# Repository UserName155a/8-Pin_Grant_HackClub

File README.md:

BOM found in .csv file

Log excluding most of the part hunting time:

11/10 ~23:00 - 11/11 ~00:40 : Working on Joystick project to use as a mouse cursor controller 

11/11 ~9:XX - 12:20? : Figuring out what parts to use and some wiring on schematics (50/50 each I think)

11/11 2:04 - 2:36 : Mapped out schematics and finalized

11/12 20:22 - 23:45 : Trying to figure out how PCB editor works and trying to connect traces (countless redos)

11/13 12:00 - 13:37 : Redesigned power management portion of sch

11/14 7:04 - 8:44 : Figuring out how PCB editor works

11/14 20:21 : 21:54 : Finalized PCB design

11/16 N/A : Part hunting and minor changes

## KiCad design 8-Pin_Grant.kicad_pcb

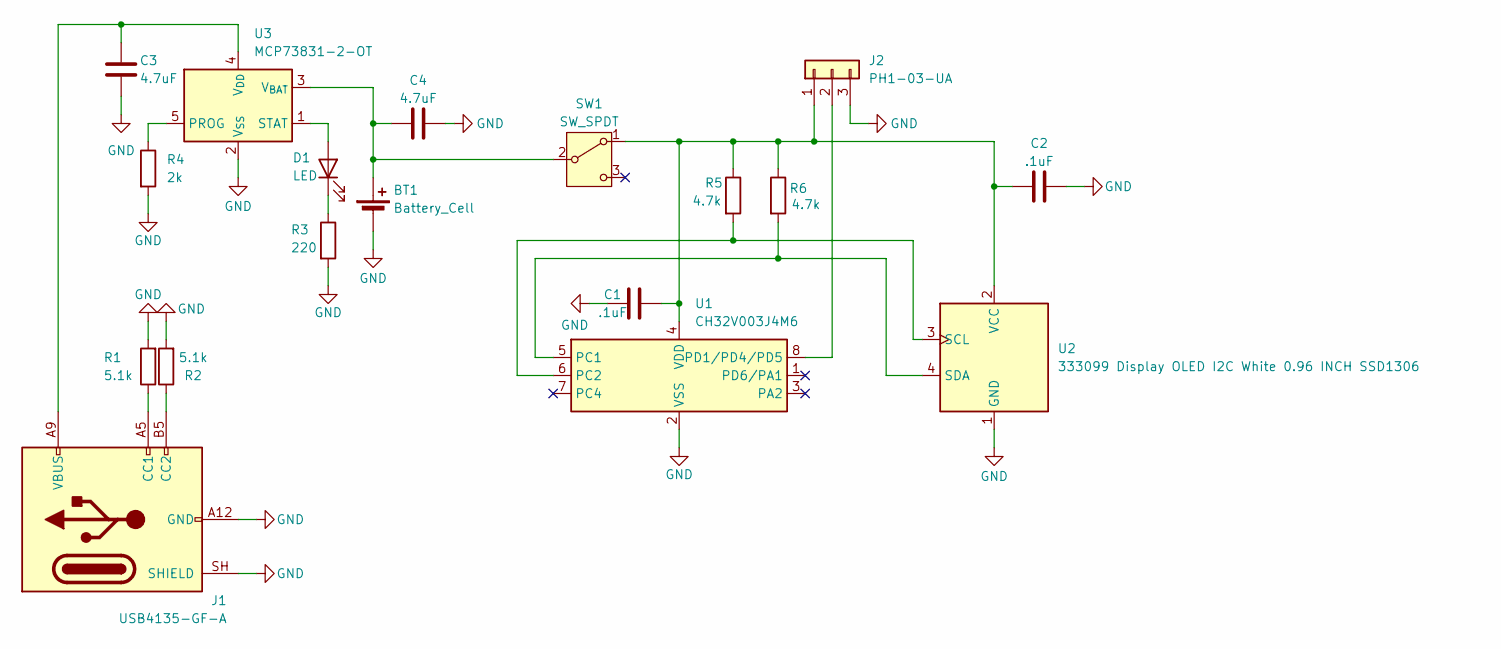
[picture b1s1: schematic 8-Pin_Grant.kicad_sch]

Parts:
BT1: Battery_Cell; JST_PH_S2B-PH-K_1x02_P2.00mm_Horizontal
C1, C2: .1uF; C_Disc_D5.0mm_W2.5mm_P5.00mm
C3, C4: 4.7uF; C_Disc_D5.0mm_W2.5mm_P5.00mm
D1: LED; LED_D3.0mm_Horizontal_O1.27mm_Z10.0mm
J1: USB4135-GF-A; USB_C_Receptacle_GCT_USB4135-GF-A_6P_TopMnt_Horizontal
J2: PH1-03-UA; PinHeader_1x03_P2.54mm_Horizontal
R1, R2: 5.1k; R_Axial_DIN0204_L3.6mm_D1.6mm_P5.08mm_Horizontal
R3: 220; R_Axial_DIN0204_L3.6mm_D1.6mm_P5.08mm_Horizontal
R4: 2k; R_Axial_DIN0204_L3.6mm_D1.6mm_P5.08mm_Horizontal
R5, R6: 4.7k; R_Axial_DIN0204_L3.6mm_D1.6mm_P5.08mm_Horizontal
SW1: SW_SPDT; SW_E-Switch_EG1224_SPDT_Angled
U1: CH32V003J4M6; JEITA_SOIC-8_3.9x4.9mm_P1.27mm
U2: 333099 Display OLED I2C White 0.96 INCH SSD1306
U3: MCP73831-2-OT; SOT-23-5

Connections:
GND: BT1.2 (-), C1.2, C2.1, C3.1, C4.1, J1.A12 (GND), J1.B12 (GND), J1.SH (SHIELD), J2.3, R1.2, R2.2, R3.2, R4.2, U1.2 (VSS), U2.1 (GND), U3.2 (V_{SS})
unnamed: BT1.1 (+), C4.2, SW1.2 (B), U3.3 (V_{BAT})
unnamed: D1.2 (A), U3.1 (STAT)
unnamed: D1.1 (K), R3.1
unnamed: J1.A5 (CC1), R1.1
unnamed: J1.B5 (CC2), R2.1
unnamed: C1.1, C2.2, J2.1, R5.1, R6.1, SW1.1 (A), U1.4 (VDD), U2.2 (VCC)
unnamed: J2.2, U1.8 (PD1/PD4/PD5)
unnamed: R6.2, U1.5 (PC1), U2.4 (SDA)
unnamed: R5.2, U1.6 (PC2), U2.3 (SCL)
unnamed: R4.1, U3.5 (PROG)
unnamed: C3.2, J1.A9 (VBUS), J1.B9 (VBUS), U3.4 (V_{DD})

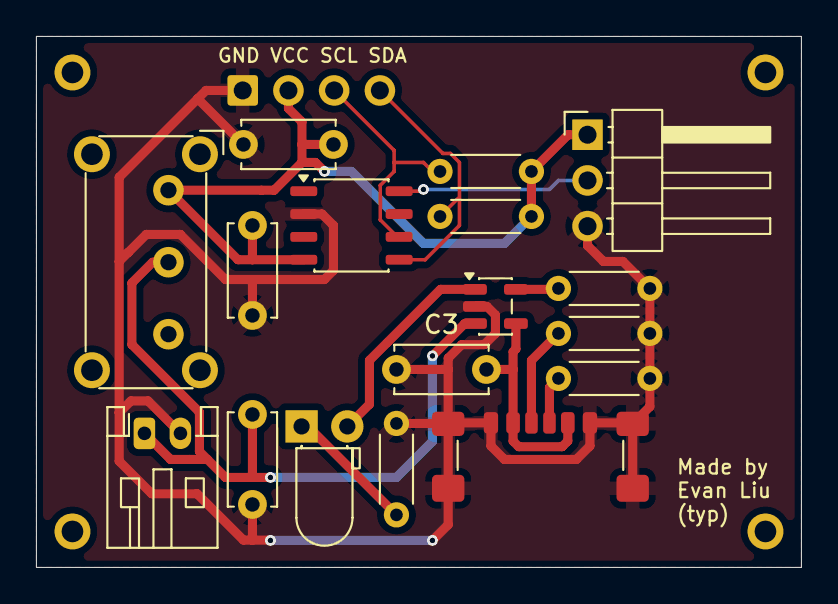
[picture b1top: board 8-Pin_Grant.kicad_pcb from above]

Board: 2 copper layers, 42.5 x 29.5 mm, 17 parts (0 on the bottom side), 12 nets.
